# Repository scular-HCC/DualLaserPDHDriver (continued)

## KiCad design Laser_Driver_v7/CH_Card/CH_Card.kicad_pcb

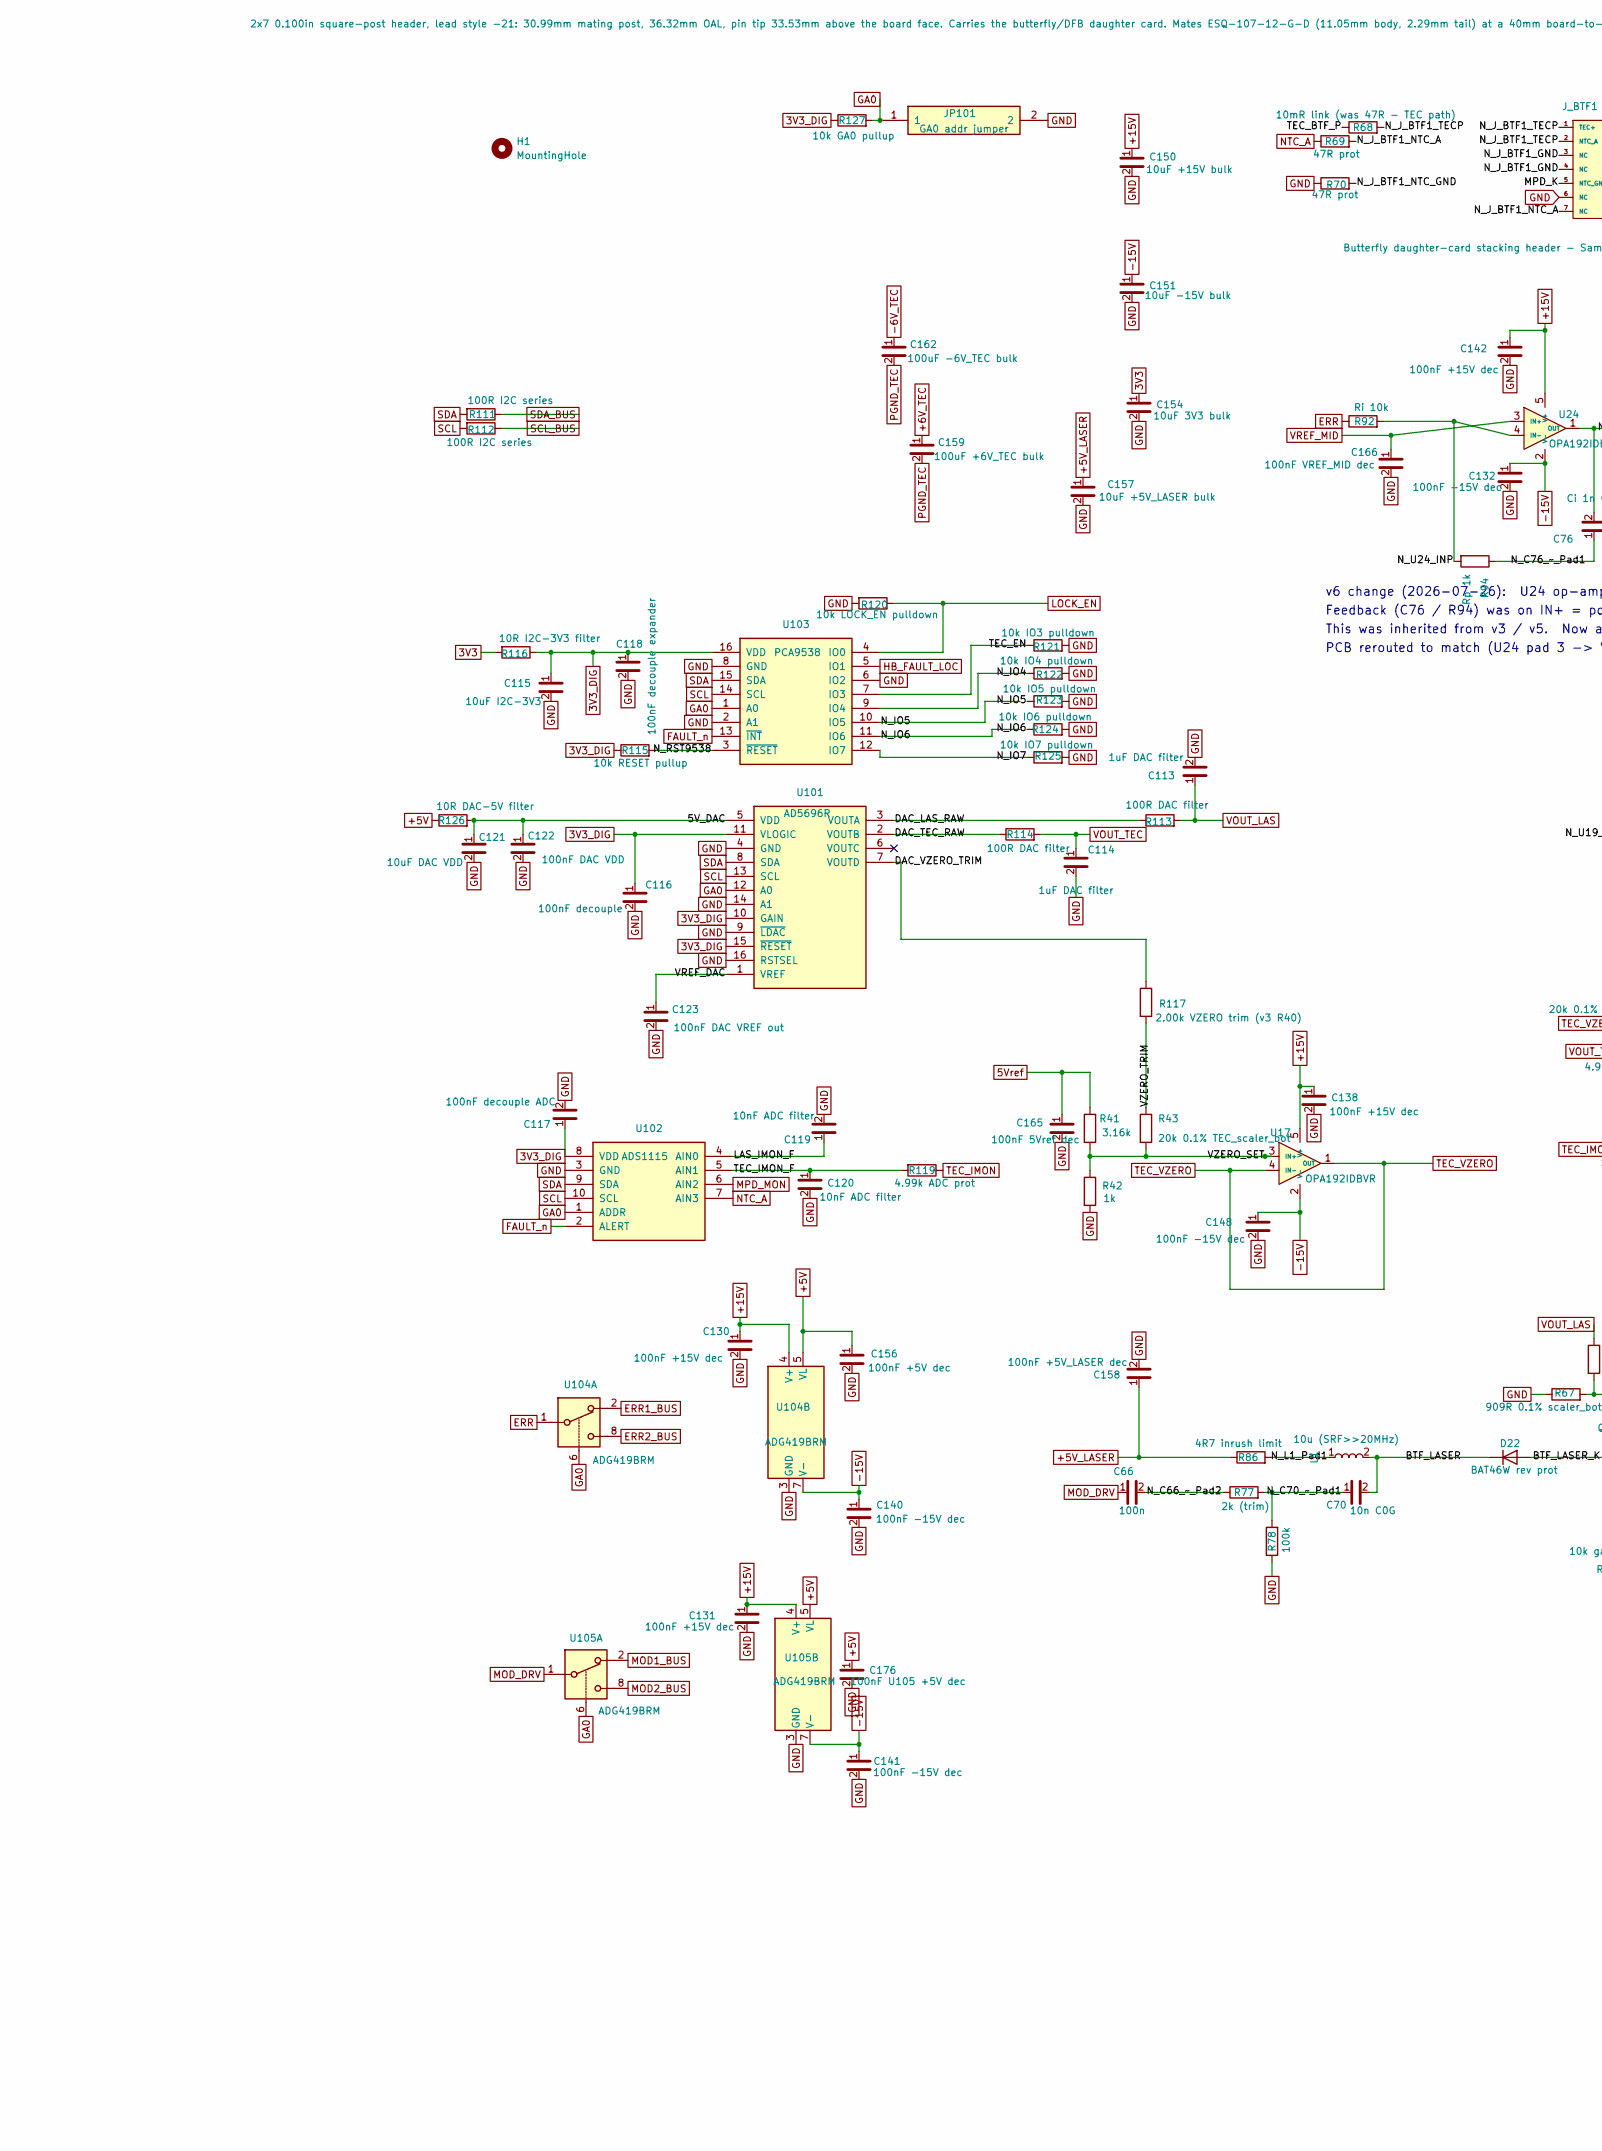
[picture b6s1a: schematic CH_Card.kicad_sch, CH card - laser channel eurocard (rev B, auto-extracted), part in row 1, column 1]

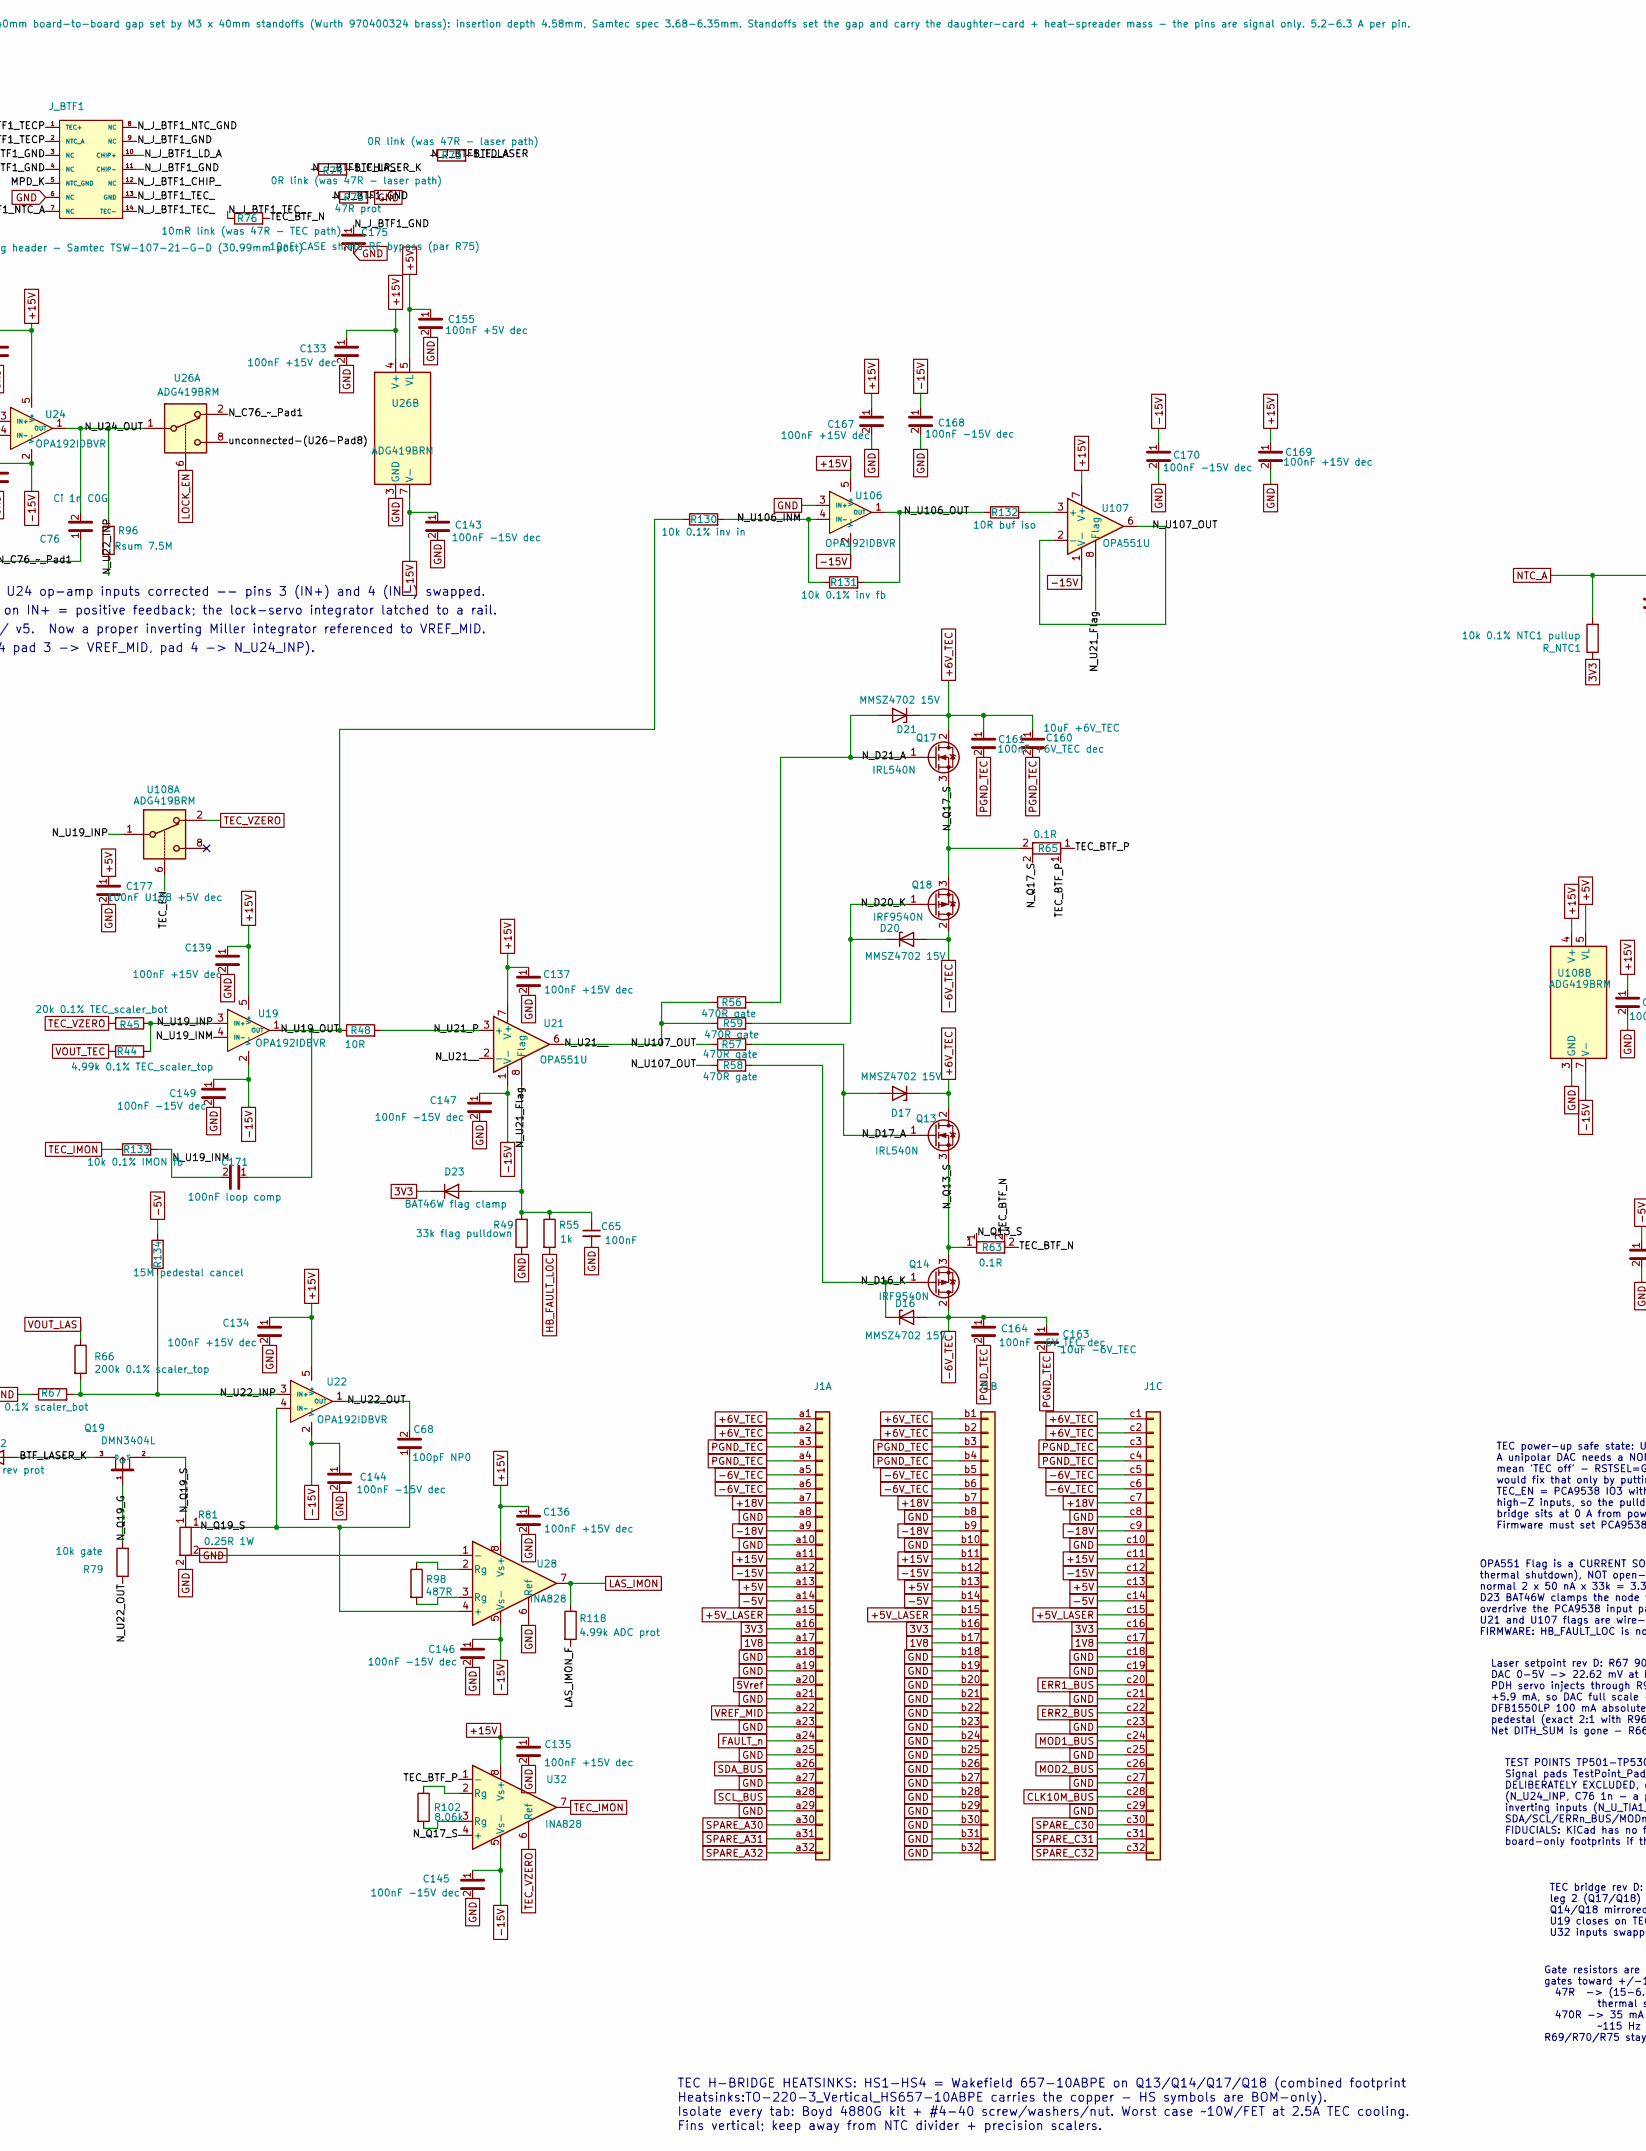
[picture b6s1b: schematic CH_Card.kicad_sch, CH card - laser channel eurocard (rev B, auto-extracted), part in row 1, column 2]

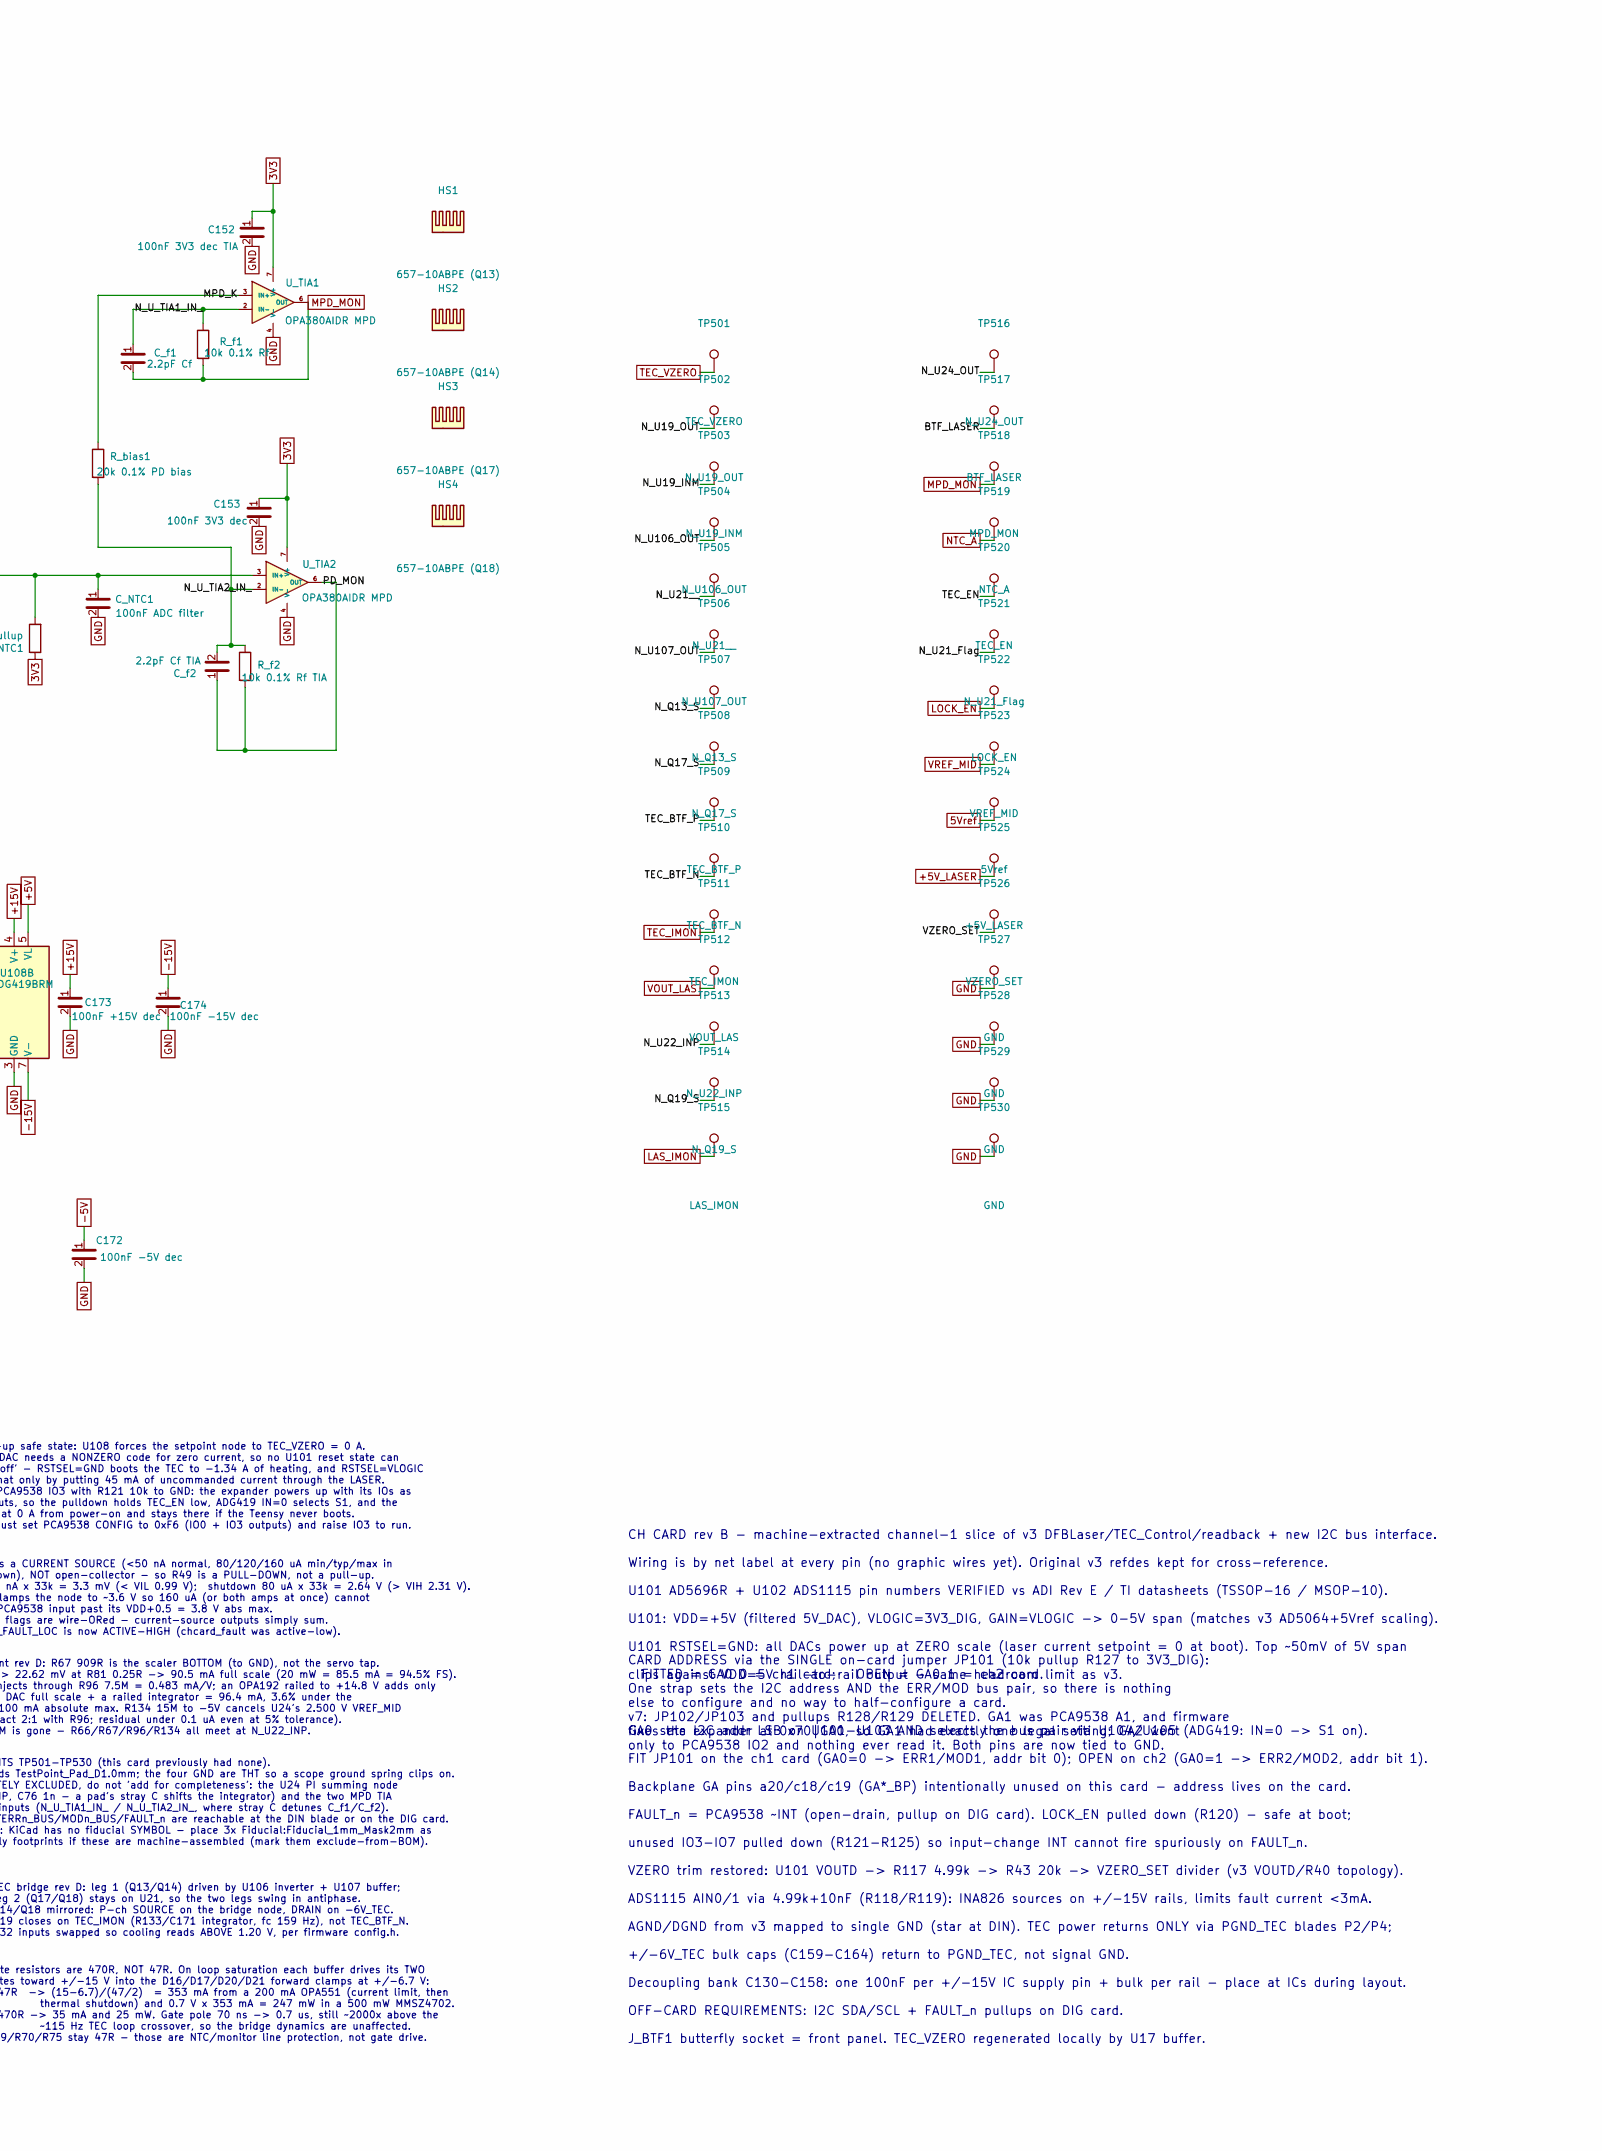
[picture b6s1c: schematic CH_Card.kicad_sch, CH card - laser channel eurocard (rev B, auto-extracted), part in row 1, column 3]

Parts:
C65: 100nF; C_0805_2012Metric_Pad1.18x1.45mm_HandSolder
C66: 100n; C_0805_2012Metric_Pad1.18x1.45mm_HandSolder
C68: 100pF NP0; C_0805_2012Metric_Pad1.18x1.45mm_HandSolder
C70: 10n C0G; C_0805_2012Metric_Pad1.18x1.45mm_HandSolder
C76: Ci 1n C0G; C_0805_2012Metric_Pad1.18x1.45mm_HandSolder
C113, C114: 1uF DAC filter; C_0805_2012Metric_Pad1.18x1.45mm_HandSolder
C115: 10uF I2C-3V3; C_0805_2012Metric_Pad1.18x1.45mm_HandSolder
C116: 100nF decouple; C_0805_2012Metric_Pad1.18x1.45mm_HandSolder
C117: 100nF decouple ADC; C_0805_2012Metric_Pad1.18x1.45mm_HandSolder
C118: 100nF decouple expander; C_0805_2012Metric_Pad1.18x1.45mm_HandSolder
C119, C120: 10nF ADC filter; C_0805_2012Metric_Pad1.18x1.45mm_HandSolder
C121: 10uF DAC VDD; C_0805_2012Metric_Pad1.18x1.45mm_HandSolder
C122: 100nF DAC VDD; C_0805_2012Metric_Pad1.18x1.45mm_HandSolder
C123: 100nF DAC VREF out; C_0805_2012Metric_Pad1.18x1.45mm_HandSolder
C130, C131, C133, C134, C135, C136, C137, C138, C139, C142, C167, C169, C173: 100nF +15V dec; C_0805_2012Metric_Pad1.18x1.45mm_HandSolder
C132, C140, C141, C143, C144, C145, C146, C147, C148, C149, C168, C170, C174: 100nF -15V dec; C_0805_2012Metric_Pad1.18x1.45mm_HandSolder
C150: 10uF +15V bulk; C_0805_2012Metric_Pad1.18x1.45mm_HandSolder
C151: 10uF -15V bulk; C_0805_2012Metric_Pad1.18x1.45mm_HandSolder
C152: 100nF 3V3 dec TIA; C_0805_2012Metric_Pad1.18x1.45mm_HandSolder
C153: 100nF 3V3 dec; C_0805_2012Metric_Pad1.18x1.45mm_HandSolder
C154: 10uF 3V3 bulk; C_0805_2012Metric_Pad1.18x1.45mm_HandSolder
C155, C156: 100nF +5V dec; C_0805_2012Metric_Pad1.18x1.45mm_HandSolder
C157: 10uF +5V_LASER bulk; C_0805_2012Metric_Pad1.18x1.45mm_HandSolder
C158: 100nF +5V_LASER dec; C_0805_2012Metric_Pad1.18x1.45mm_HandSolder
C159: 100uF +6V_TEC bulk; C_1210_3225Metric
C160: 10uF +6V_TEC; C_0805_2012Metric_Pad1.18x1.45mm_HandSolder
C161: 100nF +6V_TEC dec; C_0805_2012Metric_Pad1.18x1.45mm_HandSolder
C162: 100uF -6V_TEC bulk; C_1210_3225Metric
C163: 10uF -6V_TEC; C_0805_2012Metric_Pad1.18x1.45mm_HandSolder
C164: 100nF -6V_TEC dec; C_0805_2012Metric_Pad1.18x1.45mm_HandSolder
C165: 100nF 5Vref dec; C_0805_2012Metric_Pad1.18x1.45mm_HandSolder
C166: 100nF VREF_MID dec; C_0805_2012Metric_Pad1.18x1.45mm_HandSolder
C171: 100nF loop comp; C_0805_2012Metric_Pad1.18x1.45mm_HandSolder
C172: 100nF -5V dec; C_0805_2012Metric_Pad1.18x1.45mm_HandSolder
C175: 10nF CASE shield RF bypass (par R75); C_0805_2012Metric_Pad1.18x1.45mm_HandSolder
C176: 100nF U105 +5V dec; C_0805_2012Metric_Pad1.18x1.45mm_HandSolder
C177: 100nF U108 +5V dec; C_0805_2012Metric_Pad1.18x1.45mm_HandSolder
C_NTC1: 100nF ADC filter; C_0805_2012Metric_Pad1.18x1.45mm_HandSolder
C_f1: 2.2pF Cf; C_0402_1005Metric
C_f2: 2.2pF Cf TIA; C_0402_1005Metric
D16, D17, D20, D21: MMSZ4702 15V; D_SOD-123
D22: BAT46W rev prot; D_SOD-123
D23: BAT46W flag clamp; D_SOD-123
H1: MountingHole; MountingHole_2.7mm
HS1: 657-10ABPE (Q13)
HS2: 657-10ABPE (Q14)
HS3: 657-10ABPE (Q17)
HS4: 657-10ABPE (Q18)
J1: DIN41612_03x32_C_Split; DIN41612_C_3x32_Male_Horizontal_THT
JP101: GA0 addr jumper; PinHeader_1x02_P2.54mm_Vertical
J_BTF1: Butterfly daughter-card stacking header - Samtec 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; BTF_Card_Mezzanine_2x07_M3
L1: 10u (SRF>>20MHz); L_1812_4532Metric_Pad1.30x3.40mm_HandSolder
Q13, Q17: IRL540N; TO-220-3_Vertical_HS657-10ABPE
Q14, Q18: IRF9540N; TO-220-3_Vertical_HS657-10ABPE
Q19: DMN3404L; SOT-23
R41: 3.16k; R_0805_2012Metric_Pad1.20x1.40mm_HandSolder
R42, R55: 1k; R_0805_2012Metric_Pad1.20x1.40mm_HandSolder
R43, R45: 20k 0.1% TEC_scaler_bot; R_0805_2012Metric
R44: 4.99k 0.1% TEC_scaler_top; R_0805_2012Metric
R48: 10R; R_0805_2012Metric_Pad1.20x1.40mm_HandSolder
R49: 33k flag pulldown; R_0805_2012Metric_Pad1.20x1.40mm_HandSolder
R56, R57, R58, R59: 470R gate; R_0805_2012Metric_Pad1.20x1.40mm_HandSolder
R63, R65: 0.1R; R_2512_6332Metric
R66: 200k 0.1% scaler_top; R_0805_2012Metric
R67: 909R 0.1% scaler_bot; R_0805_2012Metric
R68, R76: 10mR link (was 47R - TEC path); R_2512_6332Metric
R69, R70, R75: 47R prot; R_0805_2012Metric_Pad1.20x1.40mm_HandSolder
R73, R74: 0R link (was 47R - laser path); R_0805_2012Metric_Pad1.20x1.40mm_HandSolder
R77: 2k (trim); R_0805_2012Metric_Pad1.20x1.40mm_HandSolder
R78: 100k; R_0805_2012Metric_Pad1.20x1.40mm_HandSolder
R79: 10k gate; R_0805_2012Metric_Pad1.20x1.40mm_HandSolder
R81: 0.25R 1W; R_2512_6332Metric
R86: 4R7 inrush limit; R_2512_6332Metric
R92: Ri 10k; R_0805_2012Metric_Pad1.20x1.40mm_HandSolder
R94: Rp 1k; R_0805_2012Metric_Pad1.20x1.40mm_HandSolder
R96: Rsum 7.5M; R_0805_2012Metric_Pad1.20x1.40mm_HandSolder
R98: 487R; R_0805_2012Metric_Pad1.20x1.40mm_HandSolder
R102: 8.06k; R_0805_2012Metric_Pad1.20x1.40mm_HandSolder
R111, R112: 100R I2C series; R_0805_2012Metric_Pad1.20x1.40mm_HandSolder
R113, R114: 100R DAC filter; R_0805_2012Metric_Pad1.20x1.40mm_HandSolder
R115: 10k RESET pullup; R_0805_2012Metric_Pad1.20x1.40mm_HandSolder
R116: 10R I2C-3V3 filter; R_0805_2012Metric_Pad1.20x1.40mm_HandSolder
R117: 2.00k VZERO trim (v3 R40); R_0805_2012Metric_Pad1.20x1.40mm_HandSolder
R118, R119: 4.99k ADC prot; R_0805_2012Metric_Pad1.20x1.40mm_HandSolder
R120: 10k LOCK_EN pulldown; R_0805_2012Metric_Pad1.20x1.40mm_HandSolder
R121: 10k IO3 pulldown; R_0805_2012Metric_Pad1.20x1.40mm_HandSolder
R122: 10k IO4 pulldown; R_0805_2012Metric_Pad1.20x1.40mm_HandSolder
R123: 10k IO5 pulldown; R_0805_2012Metric_Pad1.20x1.40mm_HandSolder
R124: 10k IO6 pulldown; R_0805_2012Metric_Pad1.20x1.40mm_HandSolder
R125: 10k IO7 pulldown; R_0805_2012Metric_Pad1.20x1.40mm_HandSolder
R126: 10R DAC-5V filter; R_0805_2012Metric_Pad1.20x1.40mm_HandSolder
R127: 10k GA0 pullup; R_0805_2012Metric_Pad1.20x1.40mm_HandSolder
R130: 10k 0.1% inv in; R_0805_2012Metric_Pad1.20x1.40mm_HandSolder
R131: 10k 0.1% inv fb; R_0805_2012Metric_Pad1.20x1.40mm_HandSolder
R132: 10R buf iso; R_0805_2012Metric_Pad1.20x1.40mm_HandSolder
R133: 10k 0.1% IMON fb; R_0805_2012Metric_Pad1.20x1.40mm_HandSolder
R134: 15M pedestal cancel; R_0805_2012Metric_Pad1.20x1.40mm_HandSolder
R_NTC1: 10k 0.1% NTC1 pullup; R_0805_2012Metric
R_bias1: 20k 0.1% PD bias; R_0805_2012Metric
R_f1: 10k 0.1% Rf; R_0805_2012Metric_Pad1.20x1.40mm_HandSolder
R_f2: 10k 0.1% Rf TIA; R_0805_2012Metric_Pad1.20x1.40mm_HandSolder
TP501: TEC_VZERO; TestPoint_Pad_D1.0mm
TP502: N_U19_OUT; TestPoint_Pad_D1.0mm
TP503: N_U19_INM; TestPoint_Pad_D1.0mm
TP504: N_U106_OUT; TestPoint_Pad_D1.0mm
TP505: N_U21__; TestPoint_Pad_D1.0mm
TP506: N_U107_OUT; TestPoint_Pad_D1.0mm
TP507: N_Q13_S; TestPoint_Pad_D1.0mm
TP508: N_Q17_S; TestPoint_Pad_D1.0mm
TP509: TEC_BTF_P; TestPoint_Pad_D1.0mm
TP510: TEC_BTF_N; TestPoint_Pad_D1.0mm
TP511: TEC_IMON; TestPoint_Pad_D1.0mm
TP512: VOUT_LAS; TestPoint_Pad_D1.0mm
TP513: N_U22_INP; TestPoint_Pad_D1.0mm
TP514: N_Q19_S; TestPoint_Pad_D1.0mm
TP515: LAS_IMON; TestPoint_Pad_D1.0mm
TP516: N_U24_OUT; TestPoint_Pad_D1.0mm
TP517: BTF_LASER; TestPoint_Pad_D1.0mm
TP518: MPD_MON; TestPoint_Pad_D1.0mm
TP519: NTC_A; TestPoint_Pad_D1.0mm
TP520: TEC_EN; TestPoint_Pad_D1.0mm
TP521: N_U21_Flag; TestPoint_Pad_D1.0mm
TP522: LOCK_EN; TestPoint_Pad_D1.0mm
TP523: VREF_MID; TestPoint_Pad_D1.0mm
TP524: 5Vref; TestPoint_Pad_D1.0mm
TP525: +5V_LASER; TestPoint_Pad_D1.0mm
TP526: VZERO_SET; TestPoint_Pad_D1.0mm
TP527, TP528, TP529, TP530: GND; TestPoint_THTPad_D1.5mm_Drill0.7mm
U17, U19, U22, U24, U106: OPA192IDBVR; SOT-23-5
U21, U107: OPA551U; SOIC-8_3.9x4.9mm_P1.27mm
U26, U104, U105, U108: ADG419BRM; MSOP-8_3x3mm_P0.65mm
U28, U32: INA828; SOIC-8_3.9x4.9mm_P1.27mm
U101: AD5696R; TSSOP-16_4.4x5mm_P0.65mm
U102: ADS1115; MSOP-10_3x3mm_P0.5mm
U103: PCA9538; TSSOP-16_4.4x5mm_P0.65mm
U_TIA1, U_TIA2: OPA380AIDR MPD; SOIC-8_3.9x4.9mm_P1.27mm

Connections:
1V8: J1.a17, J1.b17, J1.c17
3V3: C152.1, C153.1, C154.1, D23.1 (K), J1.a16, J1.b16, J1.c16, R116.2, R_NTC1.1, U_TIA1.7 (V+), U_TIA2.7 (V+)
3V3_DIG: C115.1, C116.1, C117.1, C118.1, R115.1, R116.1, R127.1, U101.10 (GAIN), U101.11 (VLOGIC), U101.15 (~RESET), U102.8 (VDD), U103.16 (VDD)
5Vref: C165.1, J1.a20, R41.1, TP524.1 (1_1)
+5V: C155.1, C156.1, C176.1, C177.1, J1.a13, J1.b13, J1.c13, R126.1, U26.5 (VL), U104.5 (VL), U105.5 (VL), U108.5 (VL)
+5V_LASER: C157.1, C158.1, J1.a15, J1.b15, J1.c15, R86.1, TP525.1 (1_1)
+6V_TEC: C159.1, C160.1, C161.1, D17.1 (K), D21.1 (K), J1.a1, J1.a2, J1.b1, J1.b2, J1.c1, J1.c2, Q13.2 (D), Q17.2 (D)
+15V: C130.1, C131.1, C133.1, C134.1, C135.1, C136.1, C137.1, C138.1, C139.1, C142.1, C150.1, C167.1, C169.1, C173.1, J1.a11, J1.b11, J1.c11, U17.5 (V+), U19.5 (V+), U21.7 (V+), U22.5 (V+), U24.5 (V+), U26.4 (V+), U28.8 (Vs+), U32.8 (Vs+), U104.4 (V+), U105.4 (V+), U106.5 (V+), U107.7 (V+), U108.4 (V+)
+18V: J1.a7, J1.b7, J1.c7
-5V: C172.1, J1.a14, J1.b14, J1.c14, R134.2
-6V_TEC: C162.1, C163.1, C164.1, D16.2 (A), D20.2 (A), J1.a5, J1.a6, J1.b5, J1.b6, J1.c5, J1.c6, Q14.2 (D), Q18.2 (D)
-15V: C132.1, C140.1, C141.1, C143.1, C144.1, C145.1, C146.1, C147.1, C148.1, C149.1, C151.1, C168.1, C170.1, C174.1, J1.a12, J1.b12, J1.c12, U17.2 (V-), U19.2 (V-), U21.1 (V-), U21.4 (V-), U21.5 (V-), U22.2 (V-), U24.2 (V-), U26.7 (V-), U28.5 (Vs-), U32.5 (Vs-), U104.7 (V-), U105.7 (V-), U106.2 (V-), U107.1 (V-), U107.4 (V-), U107.5 (V-), U108.7 (V-)
-18V: J1.a9, J1.b9, J1.c9
/5V_DAC: C121.1, C122.1, R126.2, U101.5 (VDD)
/BTF_LASER: C70.2, D22.1 (K), L1.2, R73.2, TP517.1 (1_1)
/BTF_LASER_K: D22.2 (A), Q19.3 (D), R74.2
/DAC_LAS_RAW: R113.1, U101.3 (VOUTA)
/DAC_TEC_RAW: R114.1, U101.2 (VOUTB)
/DAC_VZERO_TRIM: R117.1, U101.7 (VOUTD)
/LAS_IMON_F: C119.1, R118.2, U102.4 (AIN0)
/MPD_K: J_BTF1.5 (NTC_GND), R_bias1.1, U_TIA1.3 (IN+)
/N_C66_~_Pad2: C66.2, R77.1
/N_C70_~_Pad1: C70.1, R77.2, R78.2
/N_C76_~_Pad1: C76.1, R94.1, U26.2
/N_D16_K: D16.1 (K), Q14.1 (G), R58.2
/N_D17_A: D17.2 (A), Q13.1 (G), R57.2
/N_D20_K: D20.1 (K), Q18.1 (G), R59.2
/N_D21_A: D21.2 (A), Q17.1 (G), R56.2
/N_IO4: R122.1, U103.9 (IO4)
/N_IO5: R123.1, U103.10 (IO5)
/N_IO6: R124.1, U103.11 (IO6)
/N_IO7: R125.1, U103.12 (IO7)
/N_J_BTF1_CHIP_: J_BTF1.12 (NC), R74.1
/N_J_BTF1_GND: C175.1, J_BTF1.3 (NC), J_BTF1.4 (NC), J_BTF1.9 (NC), J_BTF1.11 (CHIP-), R75.1
/N_J_BTF1_LD_A: J_BTF1.10 (CHIP+), R73.1
/N_J_BTF1_NTC_A: J_BTF1.7 (NC), R69.2
/N_J_BTF1_NTC_GND: J_BTF1.8 (NC), R70.2
/N_J_BTF1_TECP: J_BTF1.1 (TEC+), J_BTF1.2 (NTC_A), R68.2
/N_J_BTF1_TEC_: J_BTF1.13 (GND), J_BTF1.14 (TEC-), R76.1
/N_L1_Pad1: L1.1, R86.2
/N_Q13_S: Q13.3 (S), Q14.3 (S), R63.1, TP507.1 (1_1)
/N_Q17_S: Q17.3 (S), Q18.3 (S), R65.2, TP508.1 (1_1), U32.4 (+)
/N_Q19_G: Q19.1 (G), R79.2
/N_Q19_S: C68.1, Q19.2 (S), R81.1, TP514.1 (1_1), U22.4 (IN-), U28.4 (+)
/N_RST9538: R115.2, U103.3 (~RESET)
/N_U19_INM: C171.2, R133.2, TP503.1 (1_1), U19.4 (IN-)
/N_U19_INP: R44.2, R45.1, U19.3 (IN+), U108.1
/N_U19_OUT: C171.1, R48.1, R130.1, TP502.1 (1_1), U19.1 (OUT)
/N_U21_Flag: C65.1, D23.2 (A), R49.2, R55.1, TP521.1 (1_1), U21.8 (Flag), U107.8 (Flag)
/N_U21_P: R48.2, U21.3 (+)
/N_U21__: R56.1, R59.1, TP505.1 (1_1), U21.2 (-), U21.6
/N_U22_INP: R66.2, R67.2, R96.2, R134.1, TP513.1 (1_1), U22.3 (IN+)
/N_U22_OUT: C68.2, R79.1, U22.1 (OUT)
/N_U24_INP: R92.2, R94.2, U24.4 (IN-)
/N_U24_OUT: C76.2, R96.1, TP516.1 (1_1), U24.1 (OUT), U26.1
/N_U106_INM: R130.2, R131.1, U106.4 (IN-)
/N_U106_OUT: R131.2, R132.1, TP504.1 (1_1), U106.1 (OUT)
/N_U107_OUT: R57.1, R58.1, TP506.1 (1_1), U107.2 (-), U107.6
/N_U_TIA1_IN_: C_f1.1, R_f1.1, U_TIA1.2 (IN-)
/N_U_TIA2_IN_: C_f2.2, R_bias1.2, R_f2.1, U_TIA2.2 (IN-)
/PD_MON: C_f2.1, R_f2.2, U_TIA2.6 (OUT)
/TEC_BTF_N: R63.2, R76.2, TP510.1 (1_1)
/TEC_BTF_P: R65.1, R68.1, TP509.1 (1_1), U32.1 (-)
/TEC_EN: R121.1, TP520.1 (1_1), U103.7 (IO3), U108.6
/TEC_IMON_F: C120.1, R119.2, U102.5 (AIN1)
/VREF_DAC: C123.1, U101.1 (VREF)
/VZERO_SET: R41.2, R42.1, R43.2, TP526.1 (1_1), U17.3 (IN+)
/VZERO_TRIM: R43.1, R117.2
/unconnected-(U26-Pad8): U26.8
CLK10M_BUS: J1.c28
ERR: R92.1, U104.1
ERR1_BUS: J1.c20, U104.2
ERR2_BUS: J1.c22, U104.8
FAULT_n: J1.a24, U102.2 (ALERT), U103.13 (~INT)
GA0: JP101.1, R127.2, U101.12 (A0), U102.1 (ADDR), U103.1 (A0), U104.6, U105.6
GND: C65.2, C113.2, C114.2, C115.2, C116.2, C117.2, C118.2, C119.2, C120.2, C121.2, C122.2, C123.2, C130.2, C131.2, C132.2, C133.2, C134.2, C135.2, C136.2, C137.2, C138.2, C139.2, C140.2, C141.2, C142.2, C143.2, C144.2, C145.2, C146.2, C147.2, C148.2, C149.2, C150.2, C151.2, C152.2, C153.2, C154.2, C155.2, C156.2, C157.2, C158.2, C165.2, C166.2, C167.2, C168.2, C169.2, C170.2, C172.2, C173.2, C174.2, C175.2, C176.2, C177.2, C_NTC1.2, J1.a8, J1.a10, J1.a18, J1.a19, J1.a21, J1.a23, J1.a25, J1.a27, J1.a29, J1.b8, J1.b10, J1.b18, J1.b19, J1.b20, J1.b21, J1.b22, J1.b23, J1.b24, J1.b25, J1.b26, J1.b27, J1.b28, J1.b29, J1.b30, J1.b31, J1.b32, J1.c8, J1.c10, J1.c18, J1.c19, J1.c21, J1.c23, J1.c25, J1.c27, J1.c29, JP101.2, J_BTF1.6 (NC), R42.2, R49.1, R67.1, R70.1, R75.2, R78.1, R81.2, R120.2, R121.2, R122.2, R123.2, R124.2, R125.2, TP527.1 (1_1), TP528.1 (1_1), TP529.1 (1_1), TP530.1 (1_1), U26.3 (GND), U28.1 (-), U28.6 (Ref), U101.4 (GND), U101.9 (~LDAC), U101.14 (A1), U101.16 (RSTSEL), U102.3 (GND), U103.2 (A1), U103.6 (IO2), U103.8 (GND), U104.3 (GND), U105.3 (GND), U106.3 (IN+), U108.3 (GND), U_TIA1.4 (V-), U_TIA2.4 (V-)
HB_FAULT_LOC: R55.2, U103.5 (IO1)
LAS_IMON: R118.1, TP515.1 (1_1), U28.7
LOCK_EN: R120.1, TP522.1 (1_1), U26.6, U103.4 (IO0)
MOD1_BUS: J1.c24, U105.2
MOD2_BUS: J1.c26, U105.8
MOD_DRV: C66.1, U105.1
MPD_MON: C_f1.2, R_f1.2, TP518.1 (1_1), U102.6 (AIN2), U_TIA1.6 (OUT)
NTC_A: C_NTC1.1, R69.1, R_NTC1.2, TP519.1 (1_1), U102.7 (AIN3), U_TIA2.3 (IN+)
unnamed: R98.1, U28.2 (Rg)
unnamed: R98.2, U28.3 (Rg)
unnamed: R102.1, U32.2 (Rg)
unnamed: R102.2, U32.3 (Rg)
unnamed: R132.2, U107.3 (+)
PGND_TEC: C159.2, C160.2, C161.2, C162.2, C163.2, C164.2, J1.a3, J1.a4, J1.b3, J1.b4, J1.c3, J1.c4
SCL: R112.2, U101.13 (SCL), U102.10 (SCL), U103.14 (SCL)
SCL_BUS: J1.a28, R112.1
SDA: R111.2, U101.8 (SDA), U102.9 (SDA), U103.15 (SDA)
SDA_BUS: J1.a26, R111.1
SPARE_A30: J1.a30
SPARE_A31: J1.a31
SPARE_A32: J1.a32
SPARE_C30: J1.c30
SPARE_C31: J1.c31
SPARE_C32: J1.c32
TEC_IMON: R119.1, R133.1, TP511.1 (1_1), U32.7
TEC_VZERO: R45.2, TP501.1 (1_1), U17.1 (OUT), U17.4 (IN-), U32.6 (Ref), U108.2
VOUT_LAS: C113.1, R66.1, R113.2, TP512.1 (1_1)
VOUT_TEC: C114.1, R44.1, R114.2
VREF_MID: C166.1, J1.a22, TP523.1 (1_1), U24.3 (IN+)

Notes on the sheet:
ADS1115 AIN0/1 via 4.99k+10nF (R118/R119): INA826 sources on +/-15V rails, limits fault current <3mA.
PCB rerouted to match (U24 pad 3 -> VREF_MID, pad 4 -> N_U24_INP).
Backplane GA pins a20/c18/c19 (GA*_BP) intentionally unused on this card - address lives on the card.
J_BTF1 butterfly socket = front panel. TEC_VZERO regenerated locally by U17 buffer.
Wiring is by net label at every pin (no graphic wires yet). Original v3 refdes kept for cross-reference.
VZERO trim restored: U101 VOUTD -> R117 4.99k -> R43 20k -> VZERO_SET divider (v3 VOUTD/R40 topology).
AGND/DGND from v3 mapped to single GND (star at DIN). TEC power returns ONLY via PGND_TEC blades P2/P4;
Laser setpoint rev D: R67 909R is the scaler BOTTOM (to GND), not the servo tap. DAC 0-5V -> 22.62 mV at R81 0.25R -> 90.5 mA full scale (20 mW = 85.5 mA = 94.5% FS). PDH servo injects through R96 7.5M = 0.483 mA/V; an OPA192 railed to +14.8 V adds only +5.9 mA, so DAC full scale + a railed integra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
unused IO3-IO7 pulled down (R121-R125) so input-change INT cannot fire spuriously on FAULT_n.
Feedback (C76 / R94) was on IN+ = positive feedback; the lock-servo integrator latched to a rail.
+/-6V_TEC bulk caps (C159-C164) return to PGND_TEC, not signal GND.
TEC bridge rev D: leg 1 (Q13/Q14) driven by U106 inverter + U107 buffer; leg 2 (Q17/Q18) stays on U21, so the two legs swing in antiphase. Q14/Q18 mirrored: P-ch SOURCE on the bridge node, DRAIN on -6V_TEC. U19 closes on TEC_IMON (R133/C171 integrator, fc 159 Hz), not TEC_BTF_N. U32 inputs swapped 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
FIT JP101 on the ch1 card (GA0=0 -> ERR1/MOD1, addr bit 0); OPEN on ch2 (GA0=1 -> ERR2/MOD2, addr bit 1).
This was inherited from v3 / v5. Now a proper inverting Miller integrator referenced to VREF_MID.
U101 RSTSEL=GND: all DACs power up at ZERO scale (laser current setpoint = 0 at boot). Top ~50mV of 5V span
CH CARD rev B - machine-extracted channel-1 slice of v3 DFBLaser/TEC_Control/readback + new I2C bus interface.
CARD ADDRESS via the SINGLE on-card jumper JP101 (10k pullup R127 to 3V3_DIG): FITTED = GA0 0 = ch1 card; OPEN = GA0 1 = ch2 card. One strap sets the I2C address AND the ERR/MOD bus pair, so there is nothing else to configure and no way to half-configure a card. v7: JP102/JP103 and pullups R128/R12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
U101 AD5696R + U102 ADS1115 pin numbers VERIFIED vs ADI Rev E / TI datasheets (TSSOP-16 / MSOP-10).
GA0 sets I2C addr LSB on U101-U103 AND selects the bus pair via U104/U105 (ADG419: IN=0 -> S1 on).
v6 change (2026-07-26): U24 op-amp inputs corrected -- pins 3 (IN+) and 4 (IN-) swapped.
U101: VDD=+5V (filtered 5V_DAC), VLOGIC=3V3_DIG, GAIN=VLOGIC -> 0-5V span (matches v3 AD5064+5Vref scaling).
clips against VDD=5V rail-to-rail output - same headroom limit as v3.
TEC power-up safe state: U108 forces the setpoint node to TEC_VZERO = 0 A. A unipolar DAC needs a NONZERO code for zero current, so no U101 reset state can mean 'TEC off' - RSTSEL=GND boots the TEC to -1.34 A of heating, and RSTSEL=VLOGIC would fix that only by putting 45 mA of uncommanded current 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
Decoupling bank C130-C158: one 100nF per +/-15V IC supply pin + bulk per rail - place at ICs during layout.
OPA551 Flag is a CURRENT SOURCE (<50 nA normal, 80/120/160 uA min/typ/max in thermal shutdown), NOT open-collector - so R49 is a PULL-DOWN, not a pull-up. normal 2 x 50 nA x 33k = 3.3 mV (< VIL 0.99 V); shutdown 80 uA x 33k = 2.64 V (> VIH 2.31 V). D23 BAT46W clamps the node to ~3.6 V so 160 uA (or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
OFF-CARD REQUIREMENTS: I2C SDA/SCL + FAULT_n pullups on DIG card.
FAULT_n = PCA9538 ~INT (open-drain, pullup on DIG card). LOCK_EN pulled down (R120) - safe at boot;
TEC H-BRIDGE HEATSINKS: HS1-HS4 = Wakefield 657-10ABPE on Q13/Q14/Q17/Q18 (combined footprint Heatsinks:TO-220-3_Vertical_HS657-10ABPE carries the copper - HS symbols are BOM-only). Isolate every tab: Boyd 4880G kit + #4-40 screw/washers/nut. Worst case ~10W/FET at 2.5A TEC cooling. Fins vertical; 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
TEST POINTS TP501-TP530 (this card previously had none). Signal pads TestPoint_Pad_D1.0mm; the four GND are THT so a scope ground spring clips on. DELIBERATELY EXCLUDED, do not 'add for completeness': the U24 PI summing node (N_U24_INP, C76 1n - a pad's stray C shifts the integrator) and the two MP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
Gate resistors are 470R, NOT 47R. On loop saturation each buffer drives its TWO gates toward +/-15 V into the D16/D17/D20/D21 forward clamps at +/-6.7 V: 47R -> (15-6.7)/(47/2) = 353 mA from a 200 mA OPA551 (current limit, then thermal shutdown) and 0.7 V x 353 mA = 247 mW in a 500 mW MMSZ4702. 470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

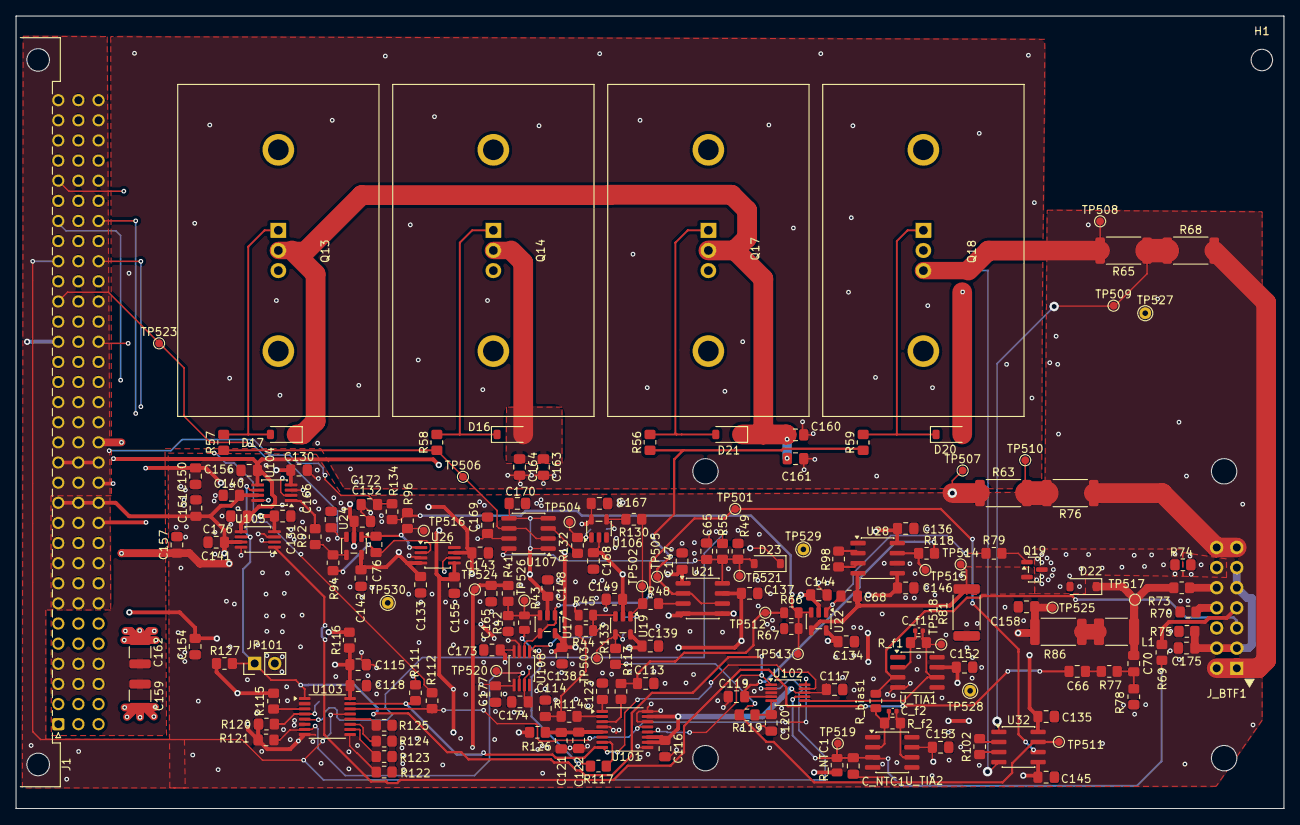
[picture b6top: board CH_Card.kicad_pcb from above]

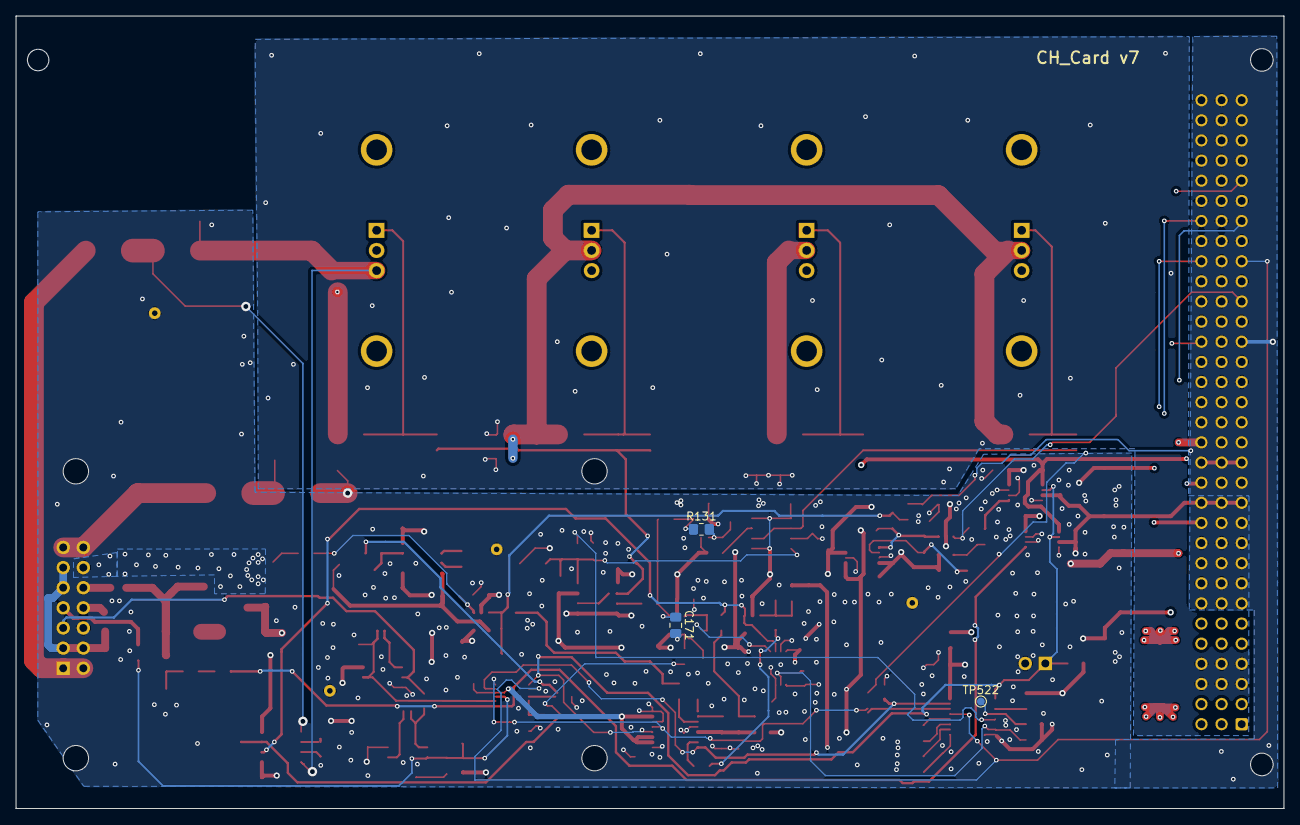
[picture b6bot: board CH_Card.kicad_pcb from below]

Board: 6 copper layers, 160.0 x 100.0 mm, 190 parts (3 on the bottom side), 97 nets.
